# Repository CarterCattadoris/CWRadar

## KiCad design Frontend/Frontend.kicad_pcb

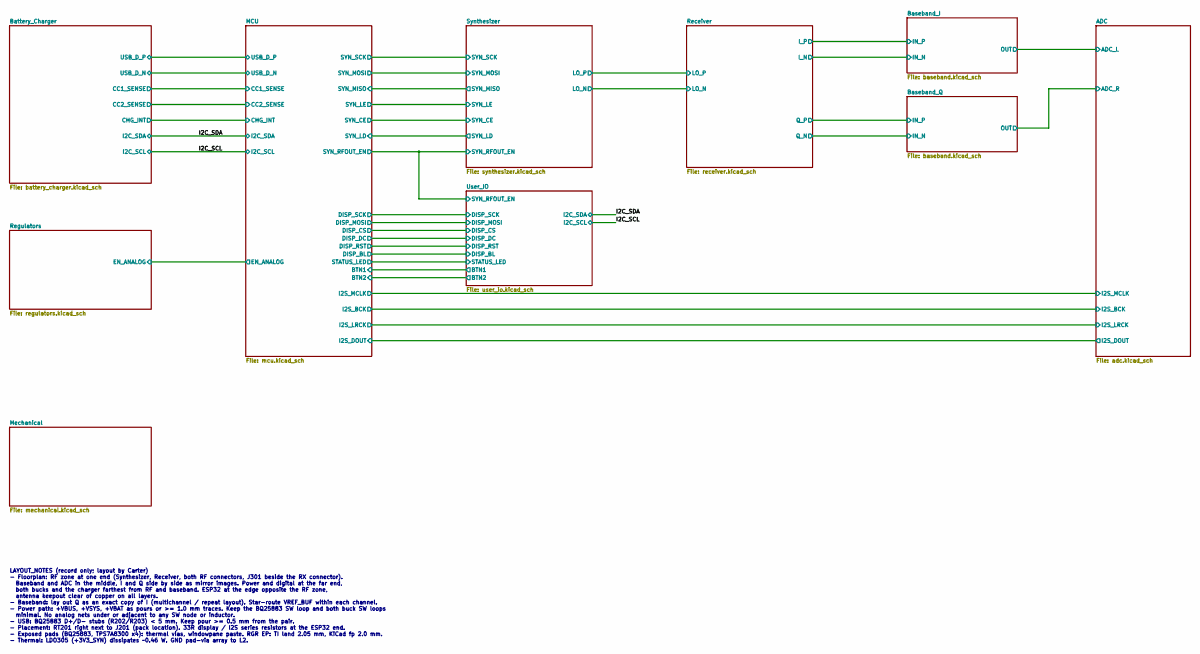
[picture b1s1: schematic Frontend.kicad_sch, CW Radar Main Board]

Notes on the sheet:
LAYOUT_NOTES (record only; layout by Carter) - Floorplan: RF zone at one end (Synthesizer, Receiver, both RF connectors, J301 beside the RX connector). Baseband and ADC in the middle, I and Q side by side as mirror images. Power and digital at the far end, both bucks and the charger farthest from R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

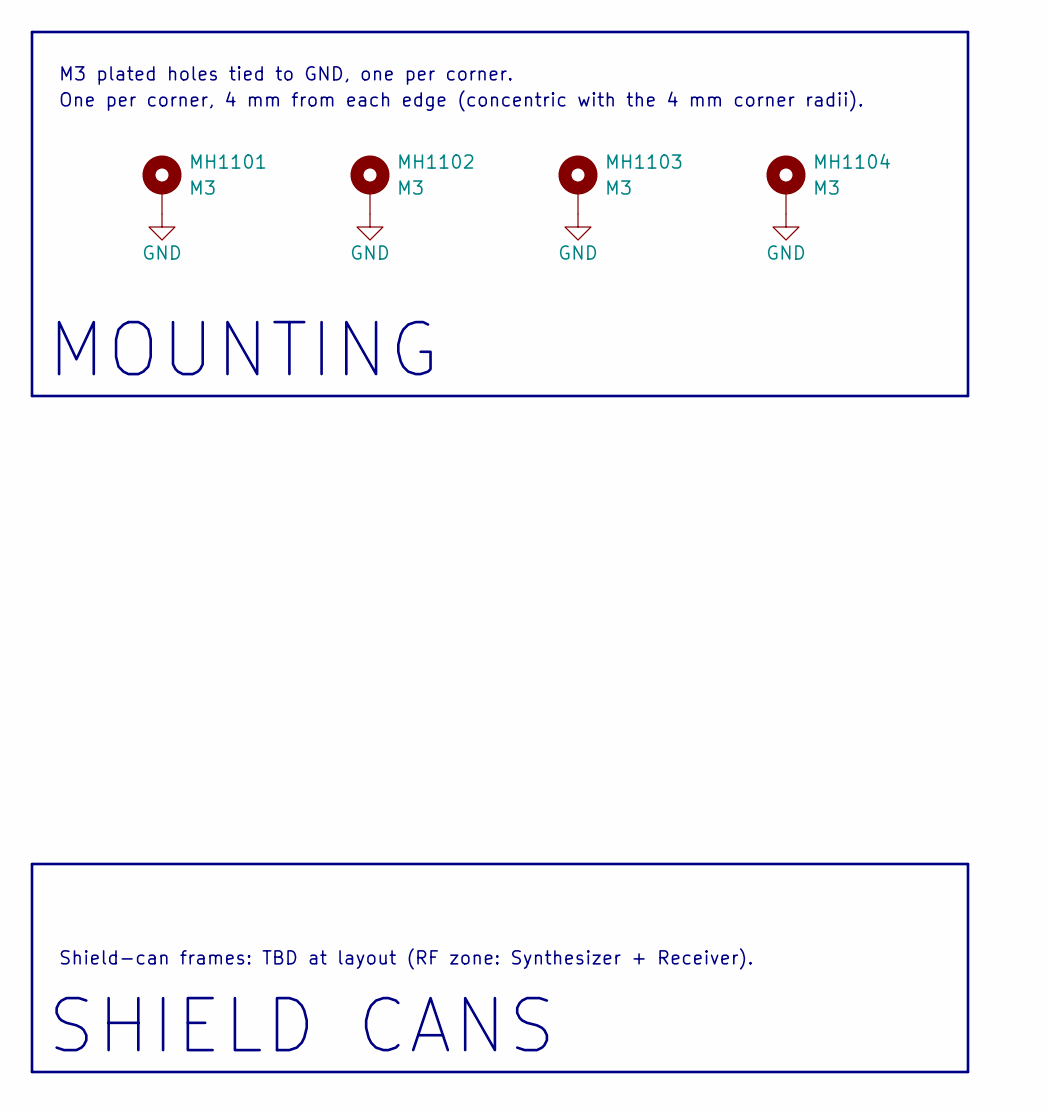
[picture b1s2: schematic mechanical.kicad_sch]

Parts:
MH1101, MH1102, MH1103, MH1104: M3; MountingHole_3.2mm_M3_Pad_Via

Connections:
GND: MH1101.1 (1_1), MH1102.1 (1_1), MH1103.1 (1_1), MH1104.1 (1_1); also elsewhere on the board

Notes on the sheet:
MOUNTING
M3 plated holes tied to GND, one per corner.
One per corner, 4 mm from each edge (concentric with the 4 mm corner radii).
Shield-can frames: TBD at layout (RF zone: Synthesizer + Receiver).
SHIELD CANS

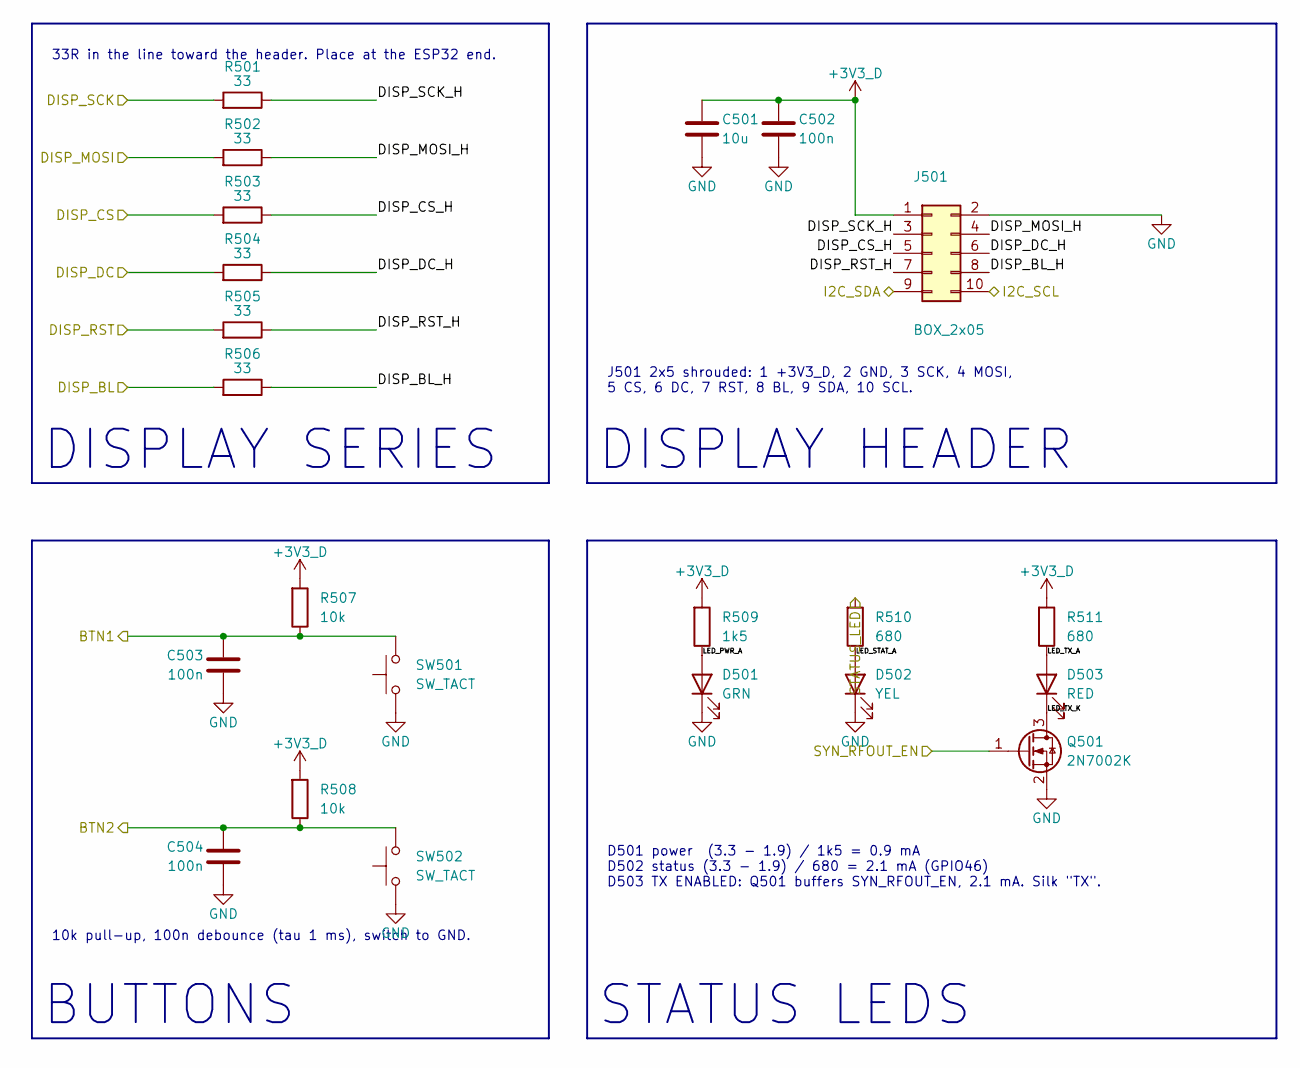
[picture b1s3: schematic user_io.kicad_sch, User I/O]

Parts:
C501: 10u; C_0805_2012Metric; Mfg Part # CL21B106KOQNNNE; LCSC C95841
C502, C503, C504: 100n; C_0402_1005Metric; Mfg Part # CL05B104KB54PNC; LCSC C307331
D501: GRN; LED_0603_1608Metric; Mfg Part # LTST-C191KGKT
D502: YEL; LED_0603_1608Metric; Mfg Part # LTST-C191KSKT
D503: RED; LED_0603_1608Metric; Mfg Part # LTST-C191KRKT
J501: BOX_2x05; IDC-Header_2x05_P2.54mm_Vertical; Mfg Part # 61201021621
Q501: 2N7002K; SOT-23; Mfg Part # 2N7002K
R501, R502, R503, R504, R505, R506: 33; R_0402_1005Metric; Mfg Part # RC0402FR-0733RL
R507, R508: 10k; R_0402_1005Metric; Mfg Part # RC0402FR-0710KL
R509: 1k5; R_0402_1005Metric; Mfg Part # ERJ-2RKF1501X
R510, R511: 680; R_0402_1005Metric; Mfg Part # RC0402FR-07680RL
SW501, SW502: SW_TACT; SW_SPST_TL3342; Mfg Part # TL3342F160QG/TR

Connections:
+3V3_D: C501.1, C502.1, J501.1, R507.1, R508.1, R509.1, R511.1; also elsewhere on the board
/I2C_SCL: J501.10; also elsewhere on the board
/I2C_SDA: J501.9; also elsewhere on the board
/MCU/BTN1: C503.1, R507.2, SW501.2; also elsewhere on the board
/MCU/BTN2: C504.1, R508.2, SW502.2; also elsewhere on the board
/MCU/DISP_BL: R506.1; also elsewhere on the board
/MCU/DISP_CS: R503.1; also elsewhere on the board
/MCU/DISP_DC: R504.1; also elsewhere on the board
/MCU/DISP_MOSI: R502.1; also elsewhere on the board
/MCU/DISP_RST: R505.1; also elsewhere on the board
/MCU/DISP_SCK: R501.1; also elsewhere on the board
/MCU/STATUS_LED: R510.1; also elsewhere on the board
/Synthesizer/SYN_RFOUT_EN: Q501.1 (G); also elsewhere on the board
/User_IO/DISP_BL_H: J501.8, R506.2
/User_IO/DISP_CS_H: J501.5, R503.2
/User_IO/DISP_DC_H: J501.6, R504.2
/User_IO/DISP_MOSI_H: J501.4, R502.2
/User_IO/DISP_RST_H: J501.7, R505.2
/User_IO/DISP_SCK_H: J501.3, R501.2
/User_IO/LED_PWR_A: D501.2 (A), R509.2
/User_IO/LED_STAT_A: D502.2 (A), R510.2
/User_IO/LED_TX_A: D503.2 (A), R511.2
/User_IO/LED_TX_K: D503.1 (K), Q501.3 (D)
GND: C501.2, C502.2, C503.2, C504.2, D501.1 (K), D502.1 (K), J501.2, Q501.2 (S), SW501.1, SW502.1; also elsewhere on the board

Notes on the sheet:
10k pull-up, 100n debounce (tau 1 ms), switch to GND.
33R in the line toward the header. Place at the ESP32 end.
DISPLAY SERIES
J501 2x5 shrouded: 1 +3V3_D, 2 GND, 3 SCK, 4 MOSI, 5 CS, 6 DC, 7 RST, 8 BL, 9 SDA, 10 SCL.
STATUS LEDS
BUTTONS
D501 power (3.3 - 1.9) / 1k5 = 0.9 mA D502 status (3.3 - 1.9) / 680 = 2.1 mA (GPIO46) D503 TX ENABLED: Q501 buffers SYN_RFOUT_EN, 2.1 mA. Silk "TX".
DISPLAY HEADER

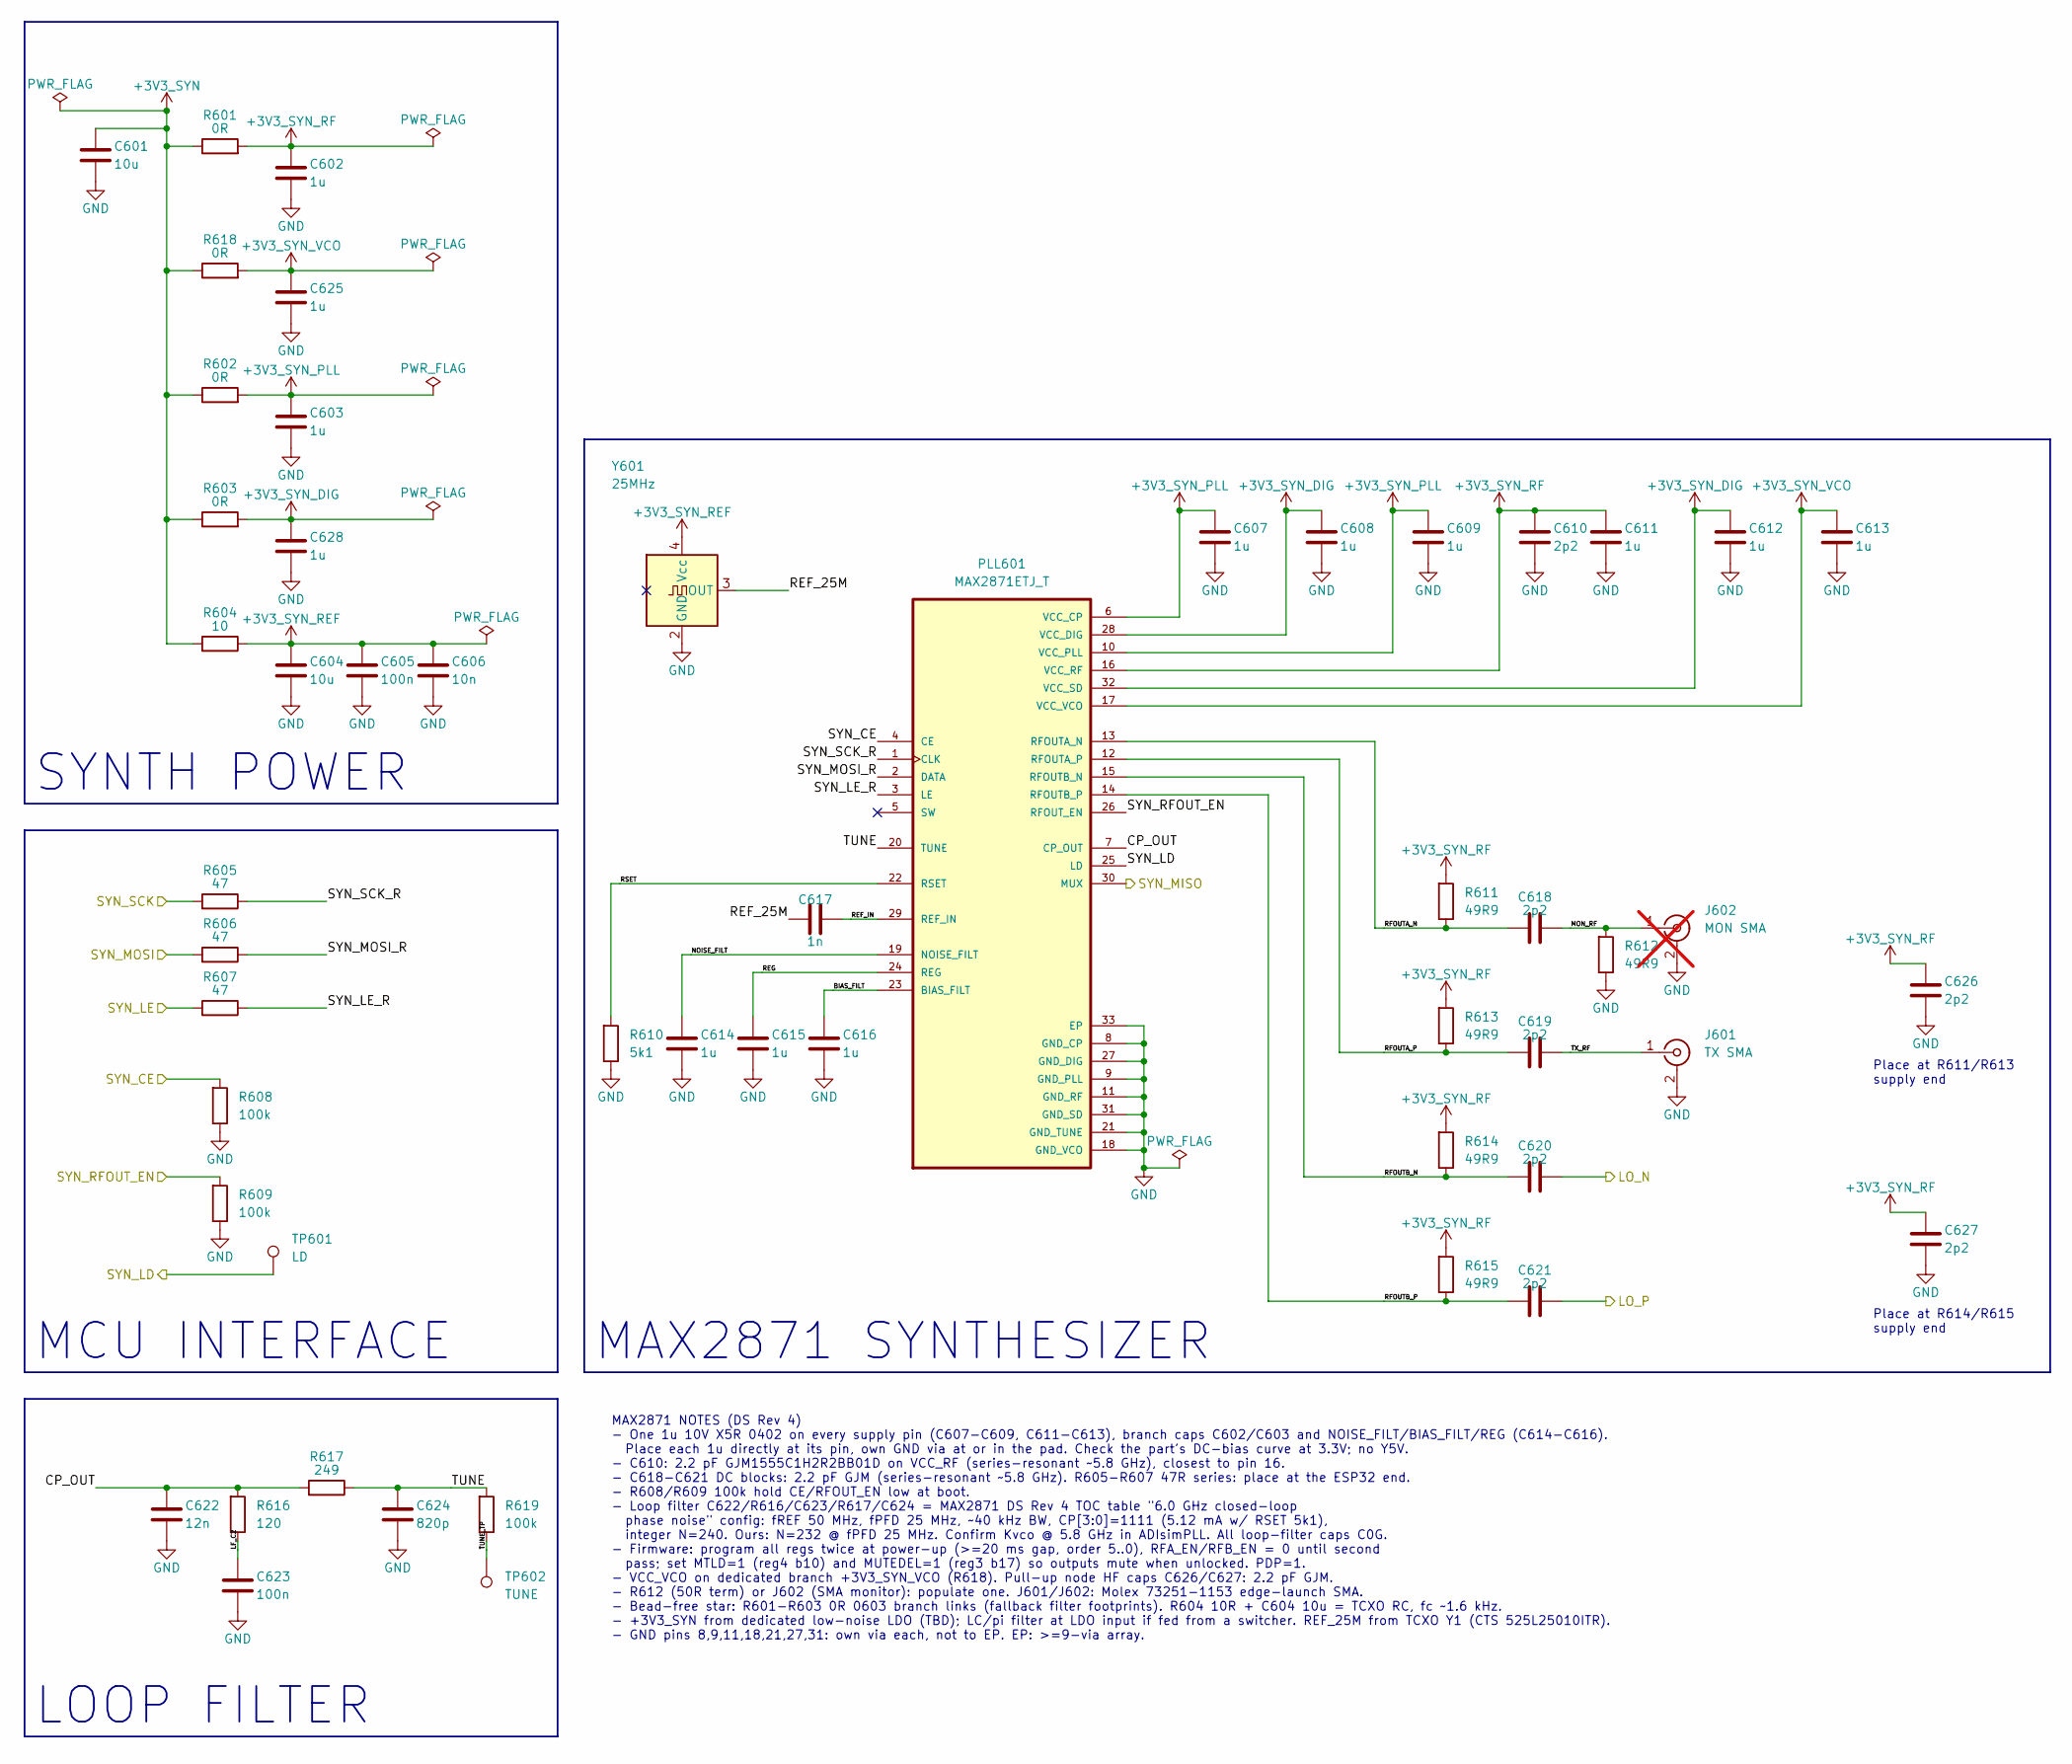
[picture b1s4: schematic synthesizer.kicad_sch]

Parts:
C601, C604: 10u; C_0805_2012Metric; Mfg Part # CL21B106KOQNNNE; LCSC C95841
C602, C603, C607, C608, C609, C611, C612, C613, C614, C615, C616, C625, C628: 1u; C_0402_1005Metric; Mfg Part # CL05A105KP5NNNC
C605: 100n; C_0402_1005Metric; Mfg Part # CL05B104KB54PNC; LCSC C307331
C606: 10n; C_0402_1005Metric; Mfg Part # CL05B103KB5NNNC
C610, C618, C619, C620, C621, C626, C627: 2p2; C_0402_1005Metric; Mfg Part # GJM1555C1H2R2BB01D
C617: 1n; C_0402_1005Metric; Mfg Part # GRM1555C1H102JA01D
C622: 12n; C_0603_1608Metric; Mfg Part # C0603C123J3GACTU
C623: 100n; C_1206_3216Metric; Mfg Part # GRM3195C2A104GA01D
C624: 820p; C_0402_1005Metric; Mfg Part # GRM1555C1H821JA01D
J601: TX SMA; SMA_Molex_73251-1153_EdgeMount_Horizontal; Mfg Part # 0732511153
J602: MON SMA; SMA_Molex_73251-1153_EdgeMount_Horizontal; Mfg Part # 0732511153; not fitted
PLL601: MAX2871ETJ_T; TQFN-32-1EP_5x5mm_P0.5mm_EP3.1x3.1mm_ThermalVias0.3; Mfg Part # MAX2871ETJ+T
R601, R602, R603, R618: 0R; R_0603_1608Metric; Mfg Part # RC0603JR-070RL; LCSC C95177
R604: 10; R_0603_1608Metric; Mfg Part # CRGP0603F10R; LCSC C2074090
R605, R606, R607: 47; R_0402_1005Metric; Mfg Part # RC0402FR-0747RL
R608, R609, R619: 100k; R_0402_1005Metric; Mfg Part # RC0402FR-07100KL
R610: 5k1; R_0402_1005Metric; Mfg Part # RC0402FR-075K1L
R611, R612, R613, R614, R615: 49R9; R_0402_1005Metric; Mfg Part # RC0402FR-0749R9L
R616: 120; R_0402_1005Metric; Mfg Part # RC0402FR-07120RL
R617: 249; R_0402_1005Metric; Mfg Part # RC0402FR-07249RL
TP601: LD; TestPoint_Pad_D1.0mm
TP602: TUNE; TestPoint_Pad_D1.0mm
Y601: 25MHz; Crystal_SMD_3225-4Pin_3.2x2.5mm; Mfg Part # 525L25010ITR

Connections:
+3V3_SYN: C601.1, R601.1, R602.1, R603.1, R604.1, R618.1; also elsewhere on the board
+3V3_SYN_DIG: C608.1, C612.1, C628.1, PLL601.28 (VCC_DIG), PLL601.32 (VCC_SD), R603.2
+3V3_SYN_PLL: C603.1, C607.1, C609.1, PLL601.6 (VCC_CP), PLL601.10 (VCC_PLL), R602.2
+3V3_SYN_REF: C604.1, C605.1, C606.1, R604.2, Y601.4 (Vcc)
+3V3_SYN_RF: C602.1, C610.1, C611.1, C626.1, C627.1, PLL601.16 (VCC_RF), R601.2, R611.1, R613.1, R614.1, R615.1
+3V3_SYN_VCO: C613.1, C625.1, PLL601.17 (VCC_VCO), R618.2
/MCU/SYN_LE: R607.1; also elsewhere on the board
/MCU/SYN_MISO: PLL601.30 (MUX); also elsewhere on the board
/MCU/SYN_MOSI: R606.1; also elsewhere on the board
/MCU/SYN_SCK: R605.1; also elsewhere on the board
/Receiver/LO_N: C620.2; also elsewhere on the board
/Receiver/LO_P: C621.2; also elsewhere on the board
/Synthesizer/BIAS_FILT: C616.1, PLL601.23 (BIAS_FILT)
/Synthesizer/CP_OUT: C622.1, PLL601.7 (CP_OUT), R616.1, R617.1
/Synthesizer/LF_C2: C623.1, R616.2
/Synthesizer/MON_RF: C618.2, J602.1 (In), R612.1
/Synthesizer/NOISE_FILT: C614.1, PLL601.19 (NOISE_FILT)
/Synthesizer/REF_25M: C617.1, Y601.3 (OUT)
/Synthesizer/REF_IN: C617.2, PLL601.29 (REF_IN)
/Synthesizer/REG: C615.1, PLL601.24 (REG)
/Synthesizer/RFOUTA_N: C618.1, PLL601.13 (RFOUTA_N), R611.2
/Synthesizer/RFOUTA_P: C619.1, PLL601.12 (RFOUTA_P), R613.2
/Synthesizer/RFOUTB_N: C620.1, PLL601.15 (RFOUTB_N), R614.2
/Synthesizer/RFOUTB_P: C621.1, PLL601.14 (RFOUTB_P), R615.2
/Synthesizer/RSET: PLL601.22 (RSET), R610.1
/Synthesizer/SYN_CE: PLL601.4 (CE), R608.1; also elsewhere on the board
/Synthesizer/SYN_LD: PLL601.25 (LD), TP601.1 (1_1); also elsewhere on the board
/Synthesizer/SYN_LE_R: PLL601.3 (LE), R607.2
/Synthesizer/SYN_MOSI_R: PLL601.2 (DATA), R606.2
/Synthesizer/SYN_RFOUT_EN: PLL601.26 (RFOUT_EN), R609.1; also elsewhere on the board
/Synthesizer/SYN_SCK_R: PLL601.1 (CLK), R605.2
/Synthesizer/TUNE: C624.1, PLL601.20 (TUNE), R617.2, R619.1
/Synthesizer/TUNE_TP: R619.2, TP602.1 (1_1)
/Synthesizer/TX_RF: C619.2, J601.1 (In)
GND: C601.2, C602.2, C603.2, C604.2, C605.2, C606.2, C607.2, C608.2, C609.2, C610.2, C611.2, C612.2, C613.2, C614.2, C615.2, C616.2, C622.2, C623.2, C624.2, C625.2, C626.2, C627.2, C628.2, J601.2 (Ext), J602.2 (Ext), PLL601.8 (GND_CP), PLL601.9 (GND_PLL), PLL601.11 (GND_RF), PLL601.18 (GND_VCO), PLL601.21 (GND_TUNE), PLL601.27 (GND_DIG), PLL601.31 (GND_SD), PLL601.33 (EP), R608.2, R609.2, R610.2, R612.2, Y601.2 (GND); also elsewhere on the board

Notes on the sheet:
SYNTH POWER
MCU INTERFACE
LOOP FILTER
Place at R611/R613 supply end
Place at R614/R615 supply end
MAX2871 SYNTHESIZER
MAX2871 NOTES (DS Rev 4) - One 1u 10V X5R 0402 on every supply pin (C607-C609, C611-C613), branch caps C602/C603 and NOISE_FILT/BIAS_FILT/REG (C614-C616). Place each 1u directly at its pin, own GND via at or in the pad. Check the part's DC-bias curve at 3.3V; no Y5V. - C610: 2.2 pF GJM1555C1H2R2BB0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

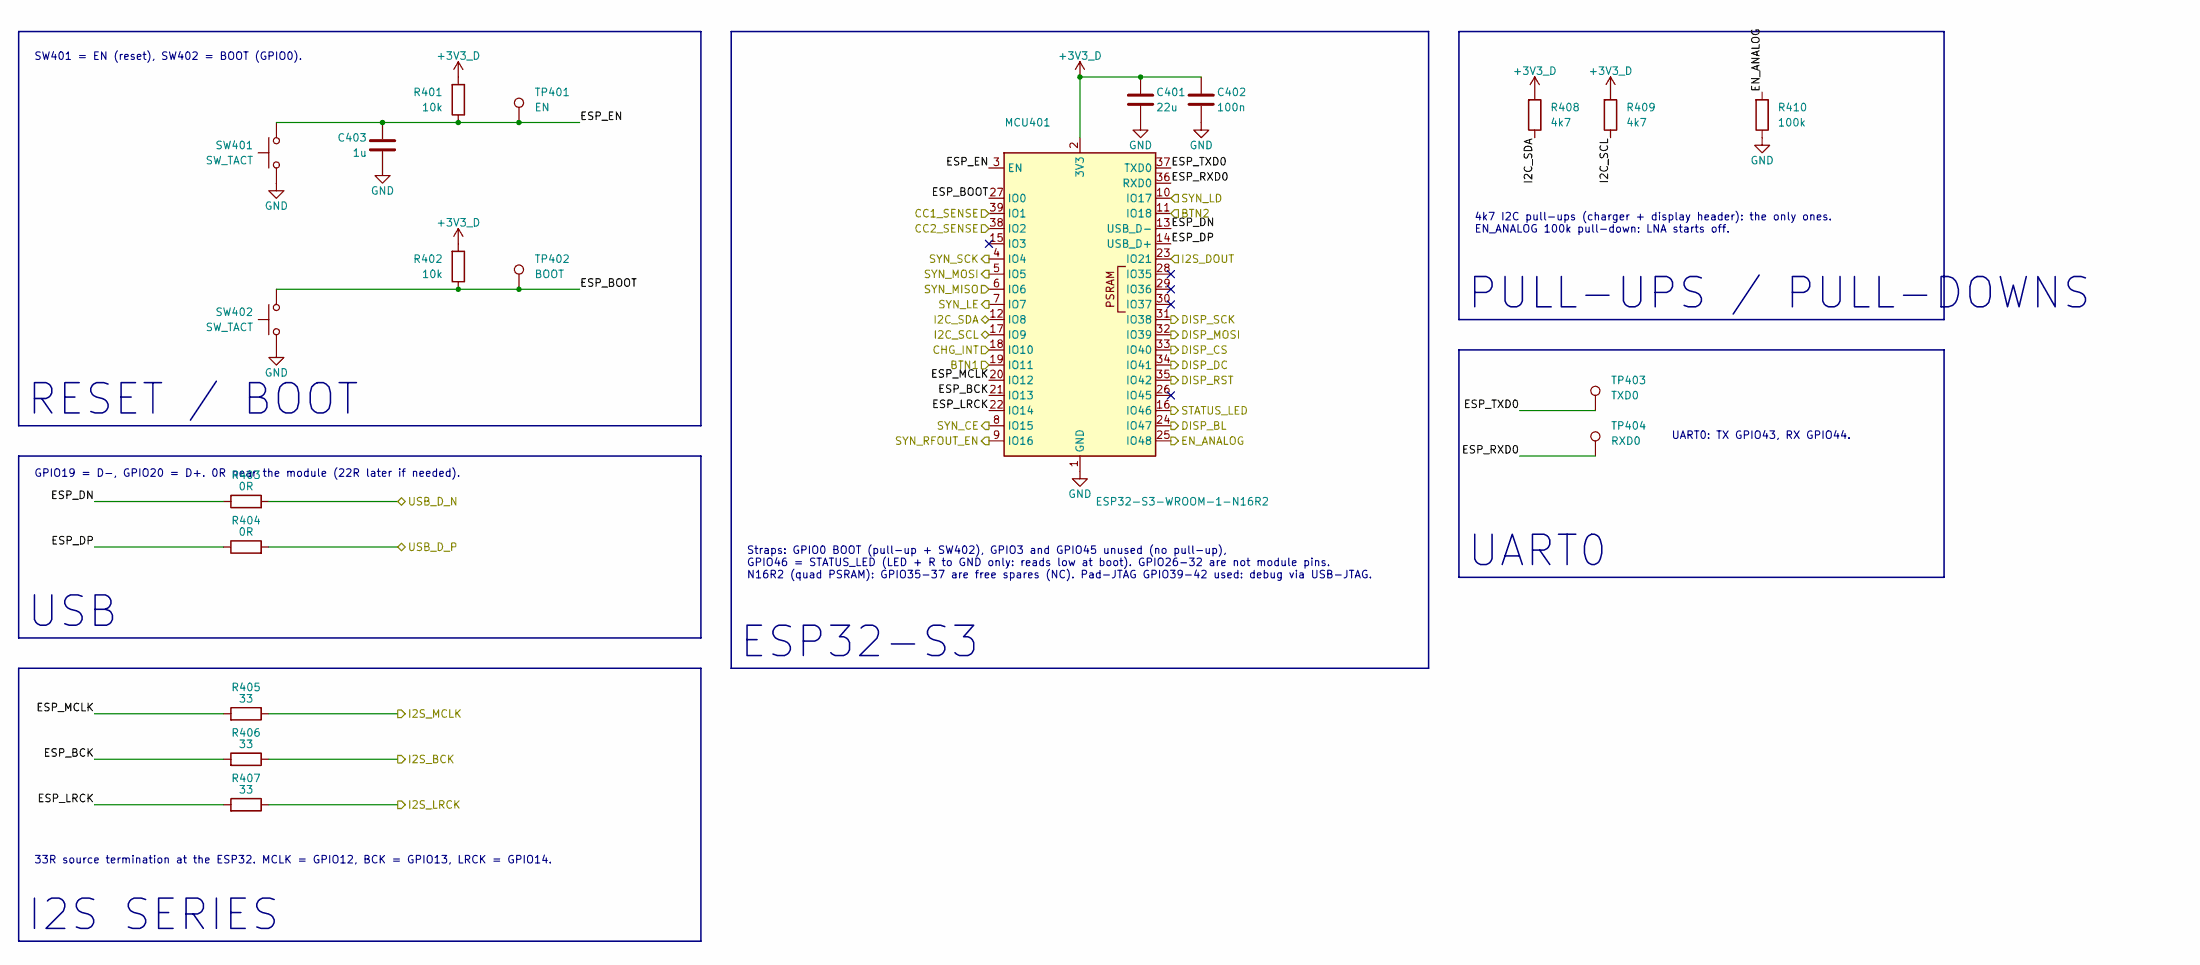
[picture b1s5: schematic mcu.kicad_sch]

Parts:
C401: 22u; C_1206_3216Metric; Mfg Part # 12063D226KAT2A
C402: 100n; C_0402_1005Metric; Mfg Part # CL05B104KB54PNC; LCSC C307331
C403: 1u; C_0402_1005Metric; Mfg Part # CL05A105KP5NNNC
MCU401: ESP32-S3-WROOM-1-N16R2; ESP32-S3-WROOM-1; Mfg Part # ESP32-S3-WROOM-1-N16R2
R401, R402: 10k; R_0402_1005Metric; Mfg Part # RC0402FR-0710KL
R403, R404: 0R; R_0402_1005Metric; Mfg Part # RC0402JR-070RL
R405, R406, R407: 33; R_0402_1005Metric; Mfg Part # RC0402FR-0733RL
R408, R409: 4k7; R_0402_1005Metric; Mfg Part # CRCW04024K70FKED
R410: 100k; R_0402_1005Metric; Mfg Part # RC0402FR-07100KL
SW401, SW402: SW_TACT; SW_SPST_TL3342; Mfg Part # TL3342F160QG/TR
TP401: EN; TestPoint_Pad_D1.0mm
TP402: BOOT; TestPoint_Pad_D1.0mm
TP403: TXD0; TestPoint_Pad_D1.0mm
TP404: RXD0; TestPoint_Pad_D1.0mm

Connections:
+3V3_D: C401.1, C402.1, MCU401.2 (3V3), R401.1, R402.1, R408.1, R409.1; also elsewhere on the board
/ADC/I2S_BCK: R406.2; also elsewhere on the board
/ADC/I2S_DOUT: MCU401.23 (IO21); also elsewhere on the board
/ADC/I2S_LRCK: R407.2; also elsewhere on the board
/ADC/I2S_MCLK: R405.2; also elsewhere on the board
/Battery_Charger/CC1_SENSE: MCU401.39 (IO1); also elsewhere on the board
/Battery_Charger/CC2_SENSE: MCU401.38 (IO2); also elsewhere on the board
/Battery_Charger/CHG_INT: MCU401.18 (IO10); also elsewhere on the board
/Battery_Charger/USB_D_N: R403.2; also elsewhere on the board
/Battery_Charger/USB_D_P: R404.2; also elsewhere on the board
/I2C_SCL: MCU401.17 (IO9), R409.2; also elsewhere on the board
/I2C_SDA: MCU401.12 (IO8), R408.2; also elsewhere on the board
/MCU/BTN1: MCU401.19 (IO11); also elsewhere on the board
/MCU/BTN2: MCU401.11 (IO18); also elsewhere on the board
/MCU/DISP_BL: MCU401.24 (IO47); also elsewhere on the board
/MCU/DISP_CS: MCU401.33 (IO40); also elsewhere on the board
/MCU/DISP_DC: MCU401.34 (IO41); also elsewhere on the board
/MCU/DISP_MOSI: MCU401.32 (IO39); also elsewhere on the board
/MCU/DISP_RST: MCU401.35 (IO42); also elsewhere on the board
/MCU/DISP_SCK: MCU401.31 (IO38); also elsewhere on the board
/MCU/EN_ANALOG: MCU401.25 (IO48), R410.1; also elsewhere on the board
/MCU/ESP_BCK: MCU401.21 (IO13), R406.1
/MCU/ESP_BOOT: MCU401.27 (IO0), R402.2, SW402.2, TP402.1 (1_1)
/MCU/ESP_DN: MCU401.13 (USB_D-), R403.1
/MCU/ESP_DP: MCU401.14 (USB_D+), R404.1
/MCU/ESP_EN: C403.1, MCU401.3 (EN), R401.2, SW401.2, TP401.1 (1_1)
/MCU/ESP_LRCK: MCU401.22 (IO14), R407.1
/MCU/ESP_MCLK: MCU401.20 (IO12), R405.1
/MCU/ESP_RXD0: MCU401.36 (RXD0), TP404.1 (1_1)
/MCU/ESP_TXD0: MCU401.37 (TXD0), TP403.1 (1_1)
/MCU/STATUS_LED: MCU401.16 (IO46); also elsewhere on the board
/MCU/SYN_LE: MCU401.7 (IO7); also elsewhere on the board
/MCU/SYN_MISO: MCU401.6 (IO6); also elsewhere on the board
/MCU/SYN_MOSI: MCU401.5 (IO5); also elsewhere on the board
/MCU/SYN_SCK: MCU401.4 (IO4); also elsewhere on the board
/Synthesizer/SYN_CE: MCU401.8 (IO15); also elsewhere on the board
/Synthesizer/SYN_LD: MCU401.10 (IO17); also elsewhere on the board
/Synthesizer/SYN_RFOUT_EN: MCU401.9 (IO16); also elsewhere on the board
GND: C401.2, C402.2, C403.2, MCU401.1 (GND), MCU401.40 (GND), MCU401.41 (GND), R410.2, SW401.1, SW402.1; also elsewhere on the board

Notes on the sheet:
4k7 I2C pull-ups (charger + display header): the only ones. EN_ANALOG 100k pull-down: LNA starts off.
33R source termination at the ESP32. MCLK = GPIO12, BCK = GPIO13, LRCK = GPIO14.
Straps: GPIO0 BOOT (pull-up + SW402), GPIO3 and GPIO45 unused (no pull-up), GPIO46 = STATUS_LED (LED + R to GND only: reads low at boot). GPIO26-32 are not module pins. N16R2 (quad PSRAM): GPIO35-37 are free spares (NC). Pad-JTAG GPIO39-42 used: debug via USB-JTAG.
USB
UART0
SW401 = EN (reset), SW402 = BOOT (GPIO0).
ESP32-S3
UART0: TX GPIO43, RX GPIO44.
PULL-UPS / PULL-DOWNS
GPIO19 = D-, GPIO20 = D+. 0R near the module (22R later if needed).
RESET / BOOT
I2S SERIES

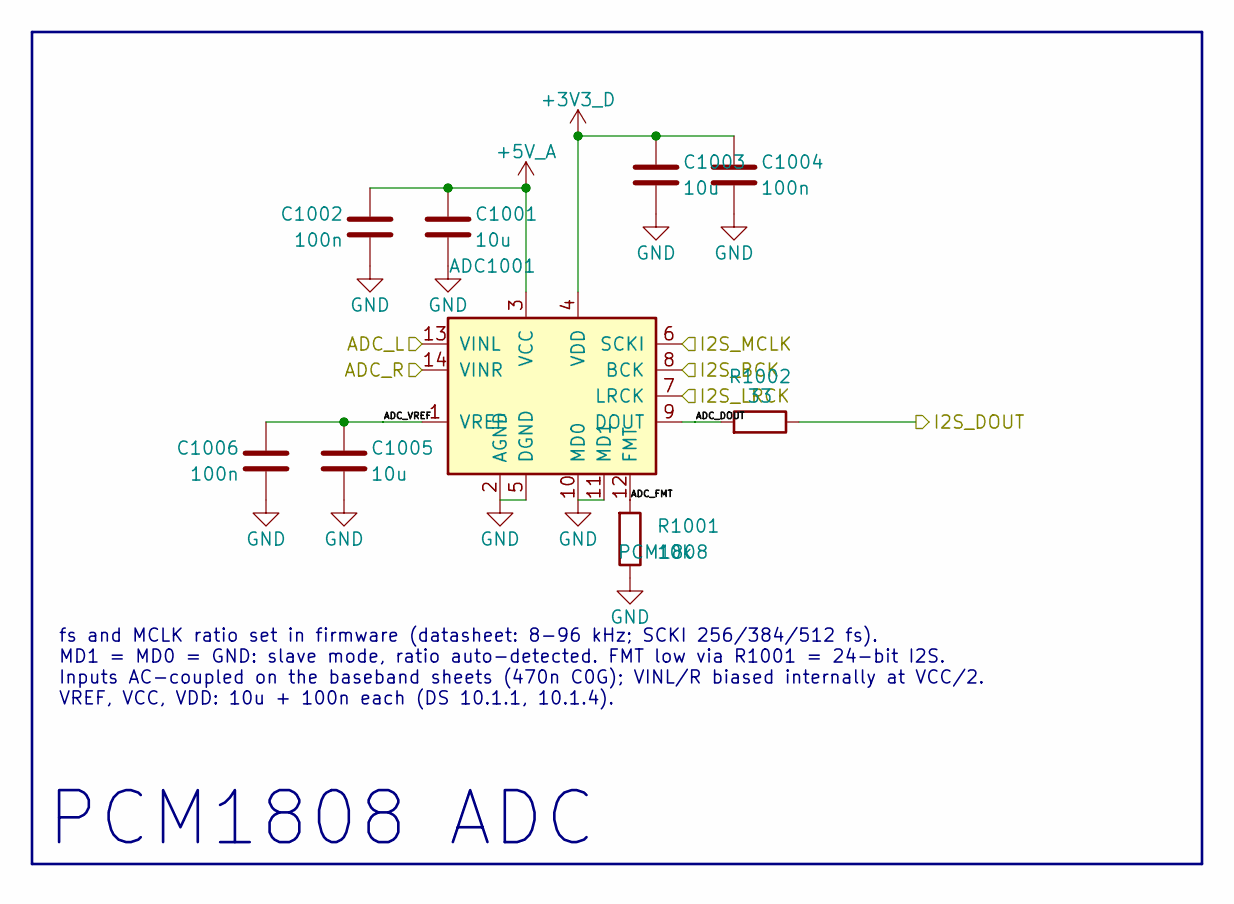
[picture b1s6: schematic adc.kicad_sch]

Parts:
ADC1001: PCM1808; TSSOP-14_4.4x5mm_P0.65mm; Mfg Part # PCM1808PWR
C1001, C1003, C1005: 10u; C_0805_2012Metric; Mfg Part # CL21B106KOQNNNE; LCSC C95841
C1002, C1004, C1006: 100n; C_0402_1005Metric; Mfg Part # CL05B104KB54PNC; LCSC C307331
R1001: 10k; R_0402_1005Metric; Mfg Part # RC0402FR-0710KL
R1002: 33; R_0402_1005Metric; Mfg Part # RC0402FR-0733RL

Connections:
+3V3_D: ADC1001.4 (VDD), C1003.1, C1004.1; also elsewhere on the board
+5V_A: ADC1001.3 (VCC), C1001.1, C1002.1; also elsewhere on the board
/ADC/ADC_DOUT: ADC1001.9 (DOUT), R1002.1
/ADC/ADC_FMT: ADC1001.12 (FMT), R1001.1
/ADC/ADC_L: ADC1001.13 (VINL); also elsewhere on the board
/ADC/ADC_R: ADC1001.14 (VINR); also elsewhere on the board
/ADC/ADC_VREF: ADC1001.1 (VREF), C1005.1, C1006.1
/ADC/I2S_BCK: ADC1001.8 (BCK); also elsewhere on the board
/ADC/I2S_DOUT: R1002.2; also elsewhere on the board
/ADC/I2S_LRCK: ADC1001.7 (LRCK); also elsewhere on the board
/ADC/I2S_MCLK: ADC1001.6 (SCKI); also elsewhere on the board
GND: ADC1001.2 (AGND), ADC1001.5 (DGND), ADC1001.10 (MD0), ADC1001.11 (MD1), C1001.2, C1002.2, C1003.2, C1004.2, C1005.2, C1006.2, R1001.2; also elsewhere on the board

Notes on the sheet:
fs and MCLK ratio set in firmware (datasheet: 8-96 kHz; SCKI 256/384/512 fs). MD1 = MD0 = GND: slave mode, ratio auto-detected. FMT low via R1001 = 24-bit I2S. Inputs AC-coupled on the baseband sheets (470n C0G); VINL/R biased internally at VCC/2. VREF, VCC, VDD: 10u + 100n each (DS 10.1.1, 10.1.4).
PCM1808 ADC

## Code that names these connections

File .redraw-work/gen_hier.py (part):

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    vpart(ref, "cwradar:100k", 40.64, y + 3.81)
    gnd(40.64, y + 7.62)
YLD = 184.15 + SH
hlabel("SYN_LD", 33.02, YLD, 180, "output")
wire((33.02, YLD), (48.26, YLD))
place("TP1", "Connector:TestPoint", 48.26, YLD, value="LD",
      fp="TestPoint:TestPoint_Pad_D1.0mm",
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
# ============================================================== LOOP FILTER
Y0 = 214.63 + SH
label("CP_OUT", 22.86, Y0, 180)
wire((22.86, Y0), (52.07, Y0))
vpart("C22", "cwradar:12n", 33.02, Y0 + 3.81); gnd(33.02, Y0 + 7.62)
vpart("R16", "cwradar:120", 43.18, Y0 + 3.81)
wire((43.18, Y0 + 7.62), (43.18, Y0 + 10.16))
label("LF_C2", 43.18, Y0 + 8.89, 90, small=True)
vpart("C23", "cwradar:100n_C0G", 43.18, Y0 + 13.97); gnd(43.18, Y0 + 17.78)
hpart("R17", "cwradar:249", 55.88, Y0)
wire((59.69, Y0), (78.74, Y0))
vpart("C24", "cwradar:820p", 66.04, Y0 + 3.81); gnd(66.04, Y0 + 7.62)
label("TUNE", 73.66, Y0, 0)
# TUNE probe point: 100k keeps probe capacitance off the loop filter
vpart("R19", "cwradar:100k", 78.74, Y0 + 3.81,
      extra={"Note": "Isolates probe capacitance from loop filter. Place R at the TUNE node."})
wire((78.74, Y0 + 7.62), (78.74, Y0 + 10.16))
label("TUNE_TP", 78.74, Y0 + 8.89, 90, small=True)
place("TP2", "Connector:TestPoint", 78.74, Y0 + 10.16, rot=180, value="TUNE",
      fp="TestPoint:TestPoint_Pad_D1.0mm",
      fields={"Reference": (81.28, Y0 + 12.7, 0, False, "right"), "Value": (81.28, Y0 + 15.24, 0, False, "right")})
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R = P["6"][0]   # right pin x

# left-side control/status labels
for pin, net in [("4", "SYN_CE"), ("1", "SYN_SCK_R"), ("2", "SYN_MOSI_R"),
                 ("3", "SYN_LE_R"), ("20", "TUNE")]:
    label(net, *P[pin], 180)
NCS.append(P["5"])
# right-side labels
for pin, net in [("26", "SYN_RFOUT_EN"), ("7", "CP_OUT"), ("25", "SYN_LD"),
                 ]:
    label(net, *P[pin], 0)
hlabel("SYN_MISO", *P["30"], 0, "output")

# supply-pin decoupling: staircase up to a 1u per pin (+ RF C0G on VCC_RF)
YT = 92.71
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
# VCO / bias decoupling and RSET: staircase down-left
YB = 165.1
for pin, cref, part, cx, net in [("23", "C16", "cwradar:1u", 127.0, "BIAS_FILT"),
                                 ("24", "C15", "cwradar:1u", 116.84, "REG"),
                                 ("19", "C14", "cwradar:1u", 106.68, "NOISE_FILT"),
                                 ("22", "R10", "cwradar:5k1", 96.52, "RSET")]:
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hpart("C17", "cwradar:1n", 125.73, ry,
      fields={"Reference": (125.73, ry - 2.794, 90, False), "Value": (125.73, ry + 3.175, 90, False)})
wire(P["29"], (129.54, ry))
label("REF_IN", 130.81, ry, 0, small=True)
label("REF_25M", 121.92, ry, 180)

# reference TCXO: CTS 525L25010ITR (25 MHz, +/-1 ppm, clipped sine), on the RC-filtered +3V3_SYN_REF branch
YX, YY = 106.68, 104.14
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gnd(*X["2"])
NCS.append(X["1"])
wire(X["3"], (121.92, YY))
label("REF_25M", 121.92, YY, 0)

# ground pins: short stubs onto a vertical bus
GX = R + 2.54
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    hpart(cref, "cwradar:2p2", DCB, Y)
    if net == "RFOUTA_P":
        wire((DCB + 3.81, Y), (J - 5.08, Y))
        label("TX_RF", DCB + 5.08, Y, 0, small=True)
        place("J1", "Connector:Conn_Coaxial", J, Y, value="TX SMA", fp="Connector_Coaxial:SMA_Molex_73251-1153_EdgeMount_Horizontal", extra=SMA,
              fields={"Reference": (J + 3.81, Y - 2.54, 0, False, "left"),
                      "Value": (J + 3.81, Y, 0, False, "left")})
        gnd(J, Y + 5.08)
    elif net == "RFOUTA_N":
        wire((DCB + 3.81, Y), (J - 5.08, Y))
        label("MON_RF", DCB + 5.08, Y, 0, small=True)
        vpart("R12", "cwradar:49R9", 238.76, Y + 3.81); gnd(238.76, Y + 7.62)
        place("J2", "Connector:Conn_Coaxial", J, Y, value="MON SMA",
              fp="Connector_Coaxial:SMA_Molex_73251-1153_EdgeMount_Horizontal", dnp=True, extra=SMA,
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
# ===================================================================== notes
text("MAX2871 NOTES (DS Rev 4)\n"
     "- One 1u 10V X5R 0402 on every supply pin (C7-C9, C11-C13), branch caps C2/C3 and NOISE_FILT/BIAS_FILT/REG (C14-C16).\n"
     "  Place each 1u directly at its pin, own GND via at or in the pad. Check the part's DC-bias curve at 3.3V; no Y5V.\n"
     "- C10: 2.2 pF GJM1555C1H2R2BB01D on VCC_RF (series-resonant ~5.8 GHz), closest to pin 16.\n"
     "- C18-C21 DC blocks: 2.2 pF GJM (series-resonant ~5.8 GHz). R5-R7 47R series: place at the ESP32 end.\n"
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        assert a[0] == b[0] or a[1] == b[1], (s1, p1, a, b)
        root_wires.append((r4(*a), r4(*b)))
# I2C also reaches the display header on User_IO: root-level local labels (no global labels)
root_labels = [("I2C_SDA", 81.28, 66.04, 0), ("I2C_SCL", 81.28, 71.12, 0),
               ("I2C_SDA", 215.9, 91.44, 0), ("I2C_SCL", 215.9, 93.98, 0)]
for p in ["I2C_SDA", "I2C_SCL"]:
    a = pin_xy("User_IO", p)
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          fields={"Reference": (129.54, 114.3, 0, False), "Value": (129.54, 116.84, 0, False)})
assert T["4"] == (134.62, YN) and T["3"] == (134.62, YP), T
wire(J["1"], T["1"])
label("RX_RF", 109.22, YP, 0, small=True)
gx2, gy2 = T["2"]  # GND pins face up on the mirrored balun
wire((gx2, gy2), (gx2, gy2 - 2.54), (gx2 - 5.08, gy2 - 2.54), (gx2 - 5.08, gy2))
gnd(gx2 - 5.08, gy2)
# balanced polarity chosen for a crossing-free layout (RF inversion flips I and Q together)
for tp, bal, cref, dem, pin in [("3", "RX_BAL_P", "C2", "DEMOD_RFIP", "22"),
                                ("4", "RX_BAL_N", "C3", "DEMOD_RFIN", "21")]:
    y = T[tp][1]
    wire(T[tp], (153.67, y))
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
# LO in: already AC-coupled on the synthesizer sheet (C620/C621). LO_P -> LOIN so the pair
# routes without crossing; LO inversion flips I and Q together, so the Doppler sign is unchanged.
for pin, lo in [("10", "LO_P"), ("9", "LO_N")]:
    px, py = D[pin]
    hlabel(lo, 160.02, py, 180, "input")
    wire((160.02, py), (px, py))
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# ADJ: open above 5 GHz, DNP footprint to VS for IIP3 tuning
ax, ay = D["19"]
wire((142.24, ay), (ax, ay))
label("DEMOD_ADJ", 162.56, ay, 0, small=True)
hpart("R3", "Device:R", 138.43, ay, value="DNP (open >5 GHz)", fp="Resistor_SMD:R_0402_1005Metric",
      dnp=True, fields={"Reference": (138.43, ay + 3.81, 90, False), "Value": (138.43, ay + 6.35, 90, False)})
rail("+5V_DEMOD", 134.62, ay)
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# ENBL low = enabled; 0R so the trace can move to an MCU GPIO later
ex, ey = D["7"]
wire((152.4, ey), (ex, ey))
label("DEMOD_ENBL", 162.56, ey, 0, small=True)
vpart("R2", "cwradar:0R_0402", 152.4, ey + 3.81)
gnd(152.4, ey + 7.62)
NCS.append(D["12"])
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     "  Keep balun-to-pin traces < ~1.4 mm and symmetric.\n"
     "- LO: LO_P/LO_N already AC-coupled on MAX2871 sheet (C620/C621). No second DC block.\n"
     "- BB out: 50 Ω diff, CM ≈ VS-1.2 V with ADJ open. DNP diff load per pair. I/Q mapping: IHI(3)->I_P, ILO(4)->I_N,\n"
     "  QHI(16)->Q_P, QLO(15)->Q_N. RF: T701 pin 3 -> RX_BAL_P -> RFIP(22), pin 4 -> RX_BAL_N -> RFIN(21).\n"
     "  LO: LO_P -> LOIN(10), LO_N -> LOIP(9) (RF and LO polarity picked for crossing-free routing).\n"
     "  Swapping the I or the Q pair (not both) flips the Doppler sign;\n"
     "  swapping the RF or LO pair inverts I and Q together and does not.\n"
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gnd(*J["A1"])
vpart("R1", "cwradar:0R", 30.48, 107.95, fields=left_f(30.48, 107.95))  # shell link, can be changed later
gnd(30.48, 111.76)
label("USB_SHIELD", 30.48, 104.14, 180, small=True)
NCS += [J["A8"], J["B8"]]
wire(J["A7"], J["B7"])
wire(J["A6"], J["B6"])
# data: connector side -> ESD2 flow-through (1->6, 3->4), as on the CR6 DAQ board
wire(J["B7"], (60.96, 81.28), (60.96, 111.76), (81.28, 111.76))
wire(J["B6"], (58.42, 86.36), (58.42, 114.3), (81.28, 114.3))
label("USBC_DN", 66.04, 111.76, 0, small=True)
label("USBC_DP", 66.04, 114.3, 0, small=True)
E = place("ESD2", "cwradar:USBLC6-2SC6", 86.36, 111.76,
          fields={"Reference": (91.44, 104.14, 0, False, "left"), "Value": (91.44, 106.68, 0, False, "left")})
rail("+VBUS", *E["5"])
gnd(*E["2"])
wire(E["6"], (134.62, 111.76))
hlabel("USB_D_N", 134.62, 111.76, 0, "bidirectional")
wire(E["4"], (134.62, 114.3))
hlabel("USB_D_P", 134.62, 114.3, 0, "bidirectional")
# BC1.2 taps to the charger, 0R so detection can be removed (keep stubs < 5 mm)
vpart("R2", "cwradar:0R_0402", 101.6, 107.95)
label("CHG_DN", 101.6, 104.14, 90)
vpart("R3", "cwradar:0R_0402", 106.68, 118.11)
label("CHG_DP", 106.68, 121.92, 270)
# CC: Rd 5.1k (sink only) + 10k series to the ESP32 ADC
E = place("ESD3", "cwradar:USBLC6-2SC6", 86.36, 71.12,
          fields={"Reference": (91.44, 63.5, 0, False, "left"), "Value": (91.44, 66.04, 0, False, "left")})
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gnd(*E["2"])
wire(J["A5"], E["1"])
wire(J["B5"], E["3"])
label("USBC_CC1", 66.04, 71.12, 0, small=True)
label("USBC_CC2", 66.04, 73.66, 0, small=True)
wire(E["6"], (96.52, 71.12), (96.52, 58.42), (107.95, 58.42))
label("USB_CC1", 96.52, 64.77, 90, small=True)
vpart("R4", "cwradar:5k1", 101.6, 62.23)
gnd(101.6, 66.04)
hpart("R5", "cwradar:10k", 111.76, 58.42)
wire((115.57, 58.42), (124.46, 58.42))
hlabel("CC1_SENSE", 124.46, 58.42, 0, "output")
wire(E["4"], (99.06, 73.66), (99.06, 86.36), (110.49, 86.36))
label("USB_CC2", 99.06, 80.01, 90, small=True)
vpart("R6", "cwradar:5k1", 104.14, 90.17)
gnd(104.14, 93.98)
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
